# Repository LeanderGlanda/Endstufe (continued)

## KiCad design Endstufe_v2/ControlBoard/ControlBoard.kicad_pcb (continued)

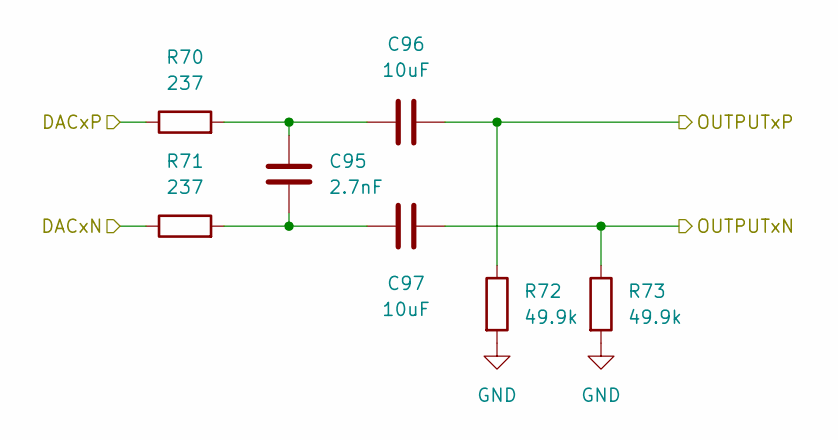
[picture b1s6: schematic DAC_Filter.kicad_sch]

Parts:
C95: 2.7nF; C_0402_1005Metric; LCSC C525230
C96, C97: 10uF; C_0805_2012Metric; LCSC Part # C440198
R70, R71: 237; R_0402_1005Metric; LCSC C2079916
R72, R73: 49.9k; R_0402_1005Metric; LCSC C854344

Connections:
/ADAU1962A/DAC1N: C97.1, R73.1; also elsewhere on the board
/ADAU1962A/DAC1P: C96.2, R72.1; also elsewhere on the board
/ADAU1962A/DAC_Filter11/DACxN: R71.1; also elsewhere on the board
/ADAU1962A/DAC_Filter11/DACxP: R70.1; also elsewhere on the board
GND: R72.2, R73.2; also elsewhere on the board
unnamed: C95.1, C97.2, R71.2
unnamed: C95.2, C96.1, R70.2

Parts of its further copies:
C62, C65, C68, C71, C74, C77, C80, C83, C86, C89, C92: 2.7nF; C_0402_1005Metric; LCSC C525230
C63, C64, C66, C67, C69, C70, C72, C73, C75, C76, C78, C79, C81, C82, C84, C85, C87, C88, C90, C91, C93, C94: 10uF; C_0805_2012Metric; LCSC Part # C440198
R26, R27, R30, R31, R34, R35, R38, R39, R42, R43, R46, R47, R50, R51, R54, R55, R58, R59, R62, R63, R66, R67: 237; R_0402_1005Metric; LCSC C2079916
R28, R29, R32, R33, R36, R37, R40, R41, R44, R45, R48, R49, R52, R53, R56, R57, R60, R61, R64, R65, R68, R69: 49.9k; R_0402_1005Metric; LCSC C854344

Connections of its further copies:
/ADAU1962A/DAC2N: C94.1, R69.1; also elsewhere on the board
/ADAU1962A/DAC2P: C93.2, R68.1; also elsewhere on the board
/ADAU1962A/DAC3N: C91.1, R65.1; also elsewhere on the board
/ADAU1962A/DAC3P: C90.2, R64.1; also elsewhere on the board
/ADAU1962A/DAC_Filter1/DACxN: R31.1; also elsewhere on the board
/ADAU1962A/DAC_Filter1/DACxP: R30.1; also elsewhere on the board
/ADAU1962A/DAC_Filter1/OUTPUTxN: C67.1, R33.1; also elsewhere on the board
/ADAU1962A/DAC_Filter1/OUTPUTxP: C66.2, R32.1; also elsewhere on the board
/ADAU1962A/DAC_Filter2/DACxN: R35.1; also elsewhere on the board
/ADAU1962A/DAC_Filter2/DACxP: R34.1; also elsewhere on the board
/ADAU1962A/DAC_Filter2/OUTPUTxN: C70.1, R37.1; also elsewhere on the board
/ADAU1962A/DAC_Filter2/OUTPUTxP: C69.2, R36.1; also elsewhere on the board
/ADAU1962A/DAC_Filter3/DACxN: R39.1; also elsewhere on the board
/ADAU1962A/DAC_Filter3/DACxP: R38.1; also elsewhere on the board
/ADAU1962A/DAC_Filter3/OUTPUTxN: C73.1, R41.1; also elsewhere on the board
/ADAU1962A/DAC_Filter3/OUTPUTxP: C72.2, R40.1; also elsewhere on the board
/ADAU1962A/DAC_Filter4/DACxN: R43.1; also elsewhere on the board
/ADAU1962A/DAC_Filter4/DACxP: R42.1; also elsewhere on the board
/ADAU1962A/DAC_Filter4/OUTPUTxN: C76.1, R45.1; also elsewhere on the board
/ADAU1962A/DAC_Filter4/OUTPUTxP: C75.2, R44.1; also elsewhere on the board
/ADAU1962A/DAC_Filter5/DACxN: R47.1; also elsewhere on the board
/ADAU1962A/DAC_Filter5/DACxP: R46.1; also elsewhere on the board
/ADAU1962A/DAC_Filter5/OUTPUTxN: C79.1, R49.1; also elsewhere on the board
/ADAU1962A/DAC_Filter5/OUTPUTxP: C78.2, R48.1; also elsewhere on the board
/ADAU1962A/DAC_Filter6/DACxN: R51.1; also elsewhere on the board
/ADAU1962A/DAC_Filter6/DACxP: R50.1; also elsewhere on the board
/ADAU1962A/DAC_Filter6/OUTPUTxN: C82.1, R53.1; also elsewhere on the board
/ADAU1962A/DAC_Filter6/OUTPUTxP: C81.2, R52.1; also elsewhere on the board
/ADAU1962A/DAC_Filter7/DACxN: R55.1; also elsewhere on the board
/ADAU1962A/DAC_Filter7/DACxP: R54.1; also elsewhere on the board
/ADAU1962A/DAC_Filter7/OUTPUTxN: C85.1, R57.1; also elsewhere on the board
/ADAU1962A/DAC_Filter7/OUTPUTxP: C84.2, R56.1; also elsewhere on the board
/ADAU1962A/DAC_Filter8/DACxN: R59.1; also elsewhere on the board
/ADAU1962A/DAC_Filter8/DACxP: R58.1; also elsewhere on the board
/ADAU1962A/DAC_Filter8/OUTPUTxN: C88.1, R61.1; also elsewhere on the board
/ADAU1962A/DAC_Filter8/OUTPUTxP: C87.2, R60.1; also elsewhere on the board
/ADAU1962A/DAC_Filter9/DACxN: R63.1; also elsewhere on the board
/ADAU1962A/DAC_Filter9/DACxP: R62.1; also elsewhere on the board
/ADAU1962A/DAC_Filter10/DACxN: R67.1; also elsewhere on the board
/ADAU1962A/DAC_Filter10/DACxP: R66.1; also elsewhere on the board
/ADAU1962A/DAC_Filter/DACxN: R27.1; also elsewhere on the board
/ADAU1962A/DAC_Filter/DACxP: R26.1; also elsewhere on the board
/ADAU1962A/DAC_Filter/OUTPUTxN: C64.1, R29.1; also elsewhere on the board
/ADAU1962A/DAC_Filter/OUTPUTxP: C63.2, R28.1; also elsewhere on the board
GND: R28.2, R29.2, R32.2, R33.2, R36.2, R37.2, R40.2, R41.2, R44.2, R45.2, R48.2, R49.2, R52.2, R53.2, R56.2, R57.2, R60.2, R61.2, R64.2, R65.2, R68.2, R69.2; also elsewhere on the board
unnamed: C62.1, C64.2, R27.2
unnamed: C62.2, C63.1, R26.2
unnamed: C65.1, C67.2, R31.2
unnamed: C65.2, C66.1, R30.2
unnamed: C68.1, C70.2, R35.2
unnamed: C68.2, C69.1, R34.2
unnamed: C71.1, C73.2, R39.2
unnamed: C71.2, C72.1, R38.2
unnamed: C74.1, C76.2, R43.2
unnamed: C74.2, C75.1, R42.2
unnamed: C77.1, C79.2, R47.2
unnamed: C77.2, C78.1, R46.2
unnamed: C80.1, C82.2, R51.2
unnamed: C80.2, C81.1, R50.2
unnamed: C83.1, C85.2, R55.2
unnamed: C83.2, C84.1, R54.2
unnamed: C86.1, C88.2, R59.2
unnamed: C86.2, C87.1, R58.2
unnamed: C89.1, C91.2, R63.2
unnamed: C89.2, C90.1, R62.2
unnamed: C92.1, C94.2, R67.2
unnamed: C92.2, C93.1, R66.2

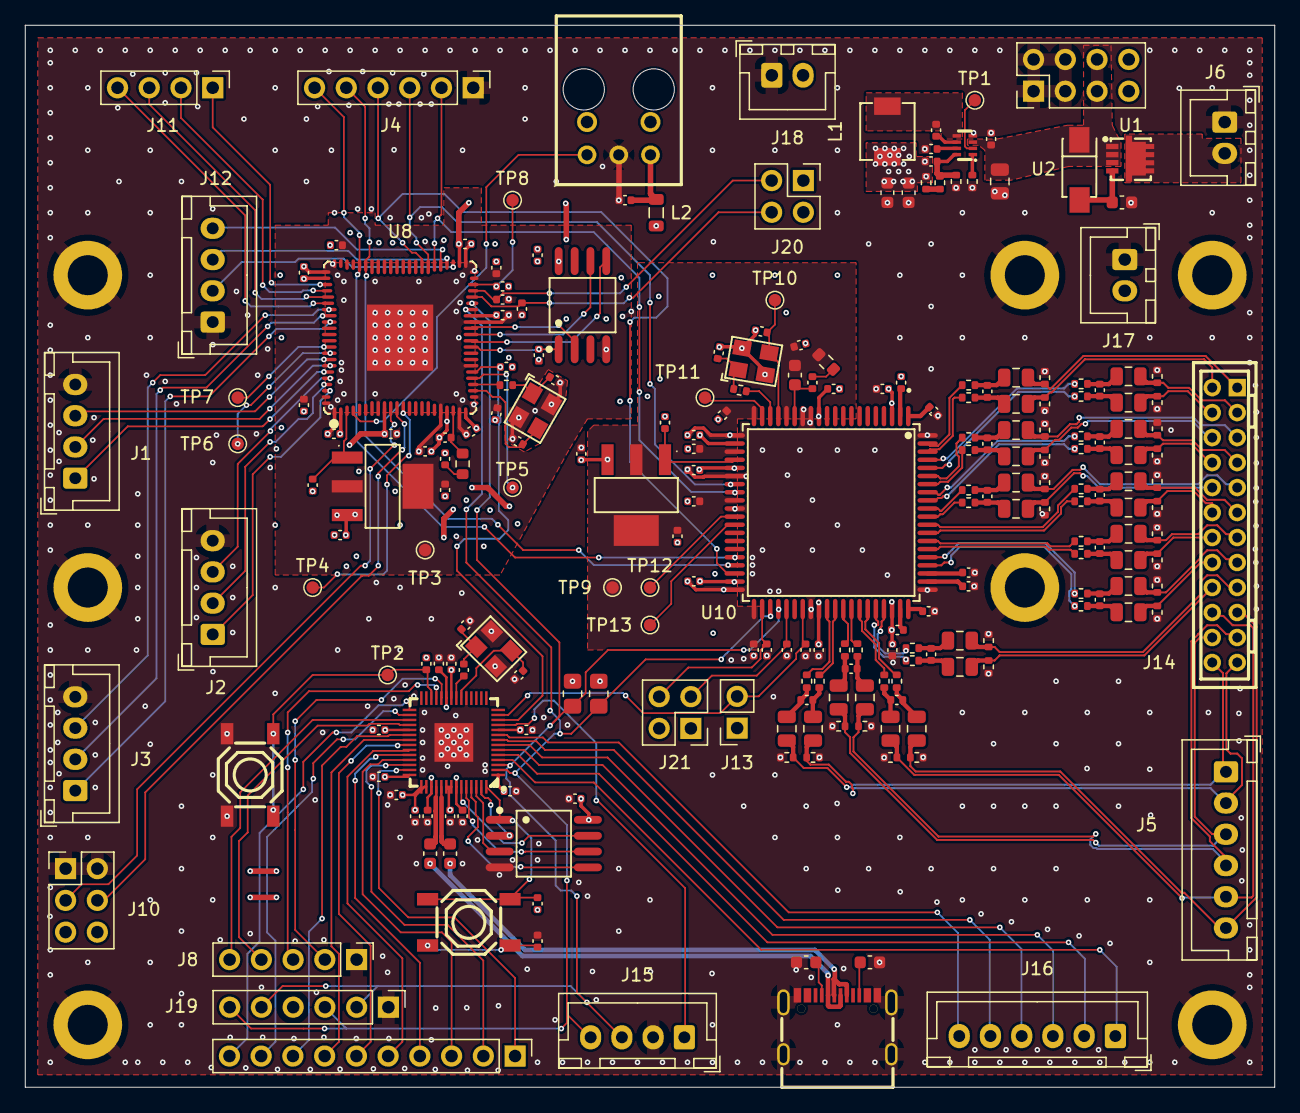
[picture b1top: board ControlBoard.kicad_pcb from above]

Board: 4 copper layers, 100.0 x 85.0 mm, 237 parts (0 on the bottom side), 188 nets.

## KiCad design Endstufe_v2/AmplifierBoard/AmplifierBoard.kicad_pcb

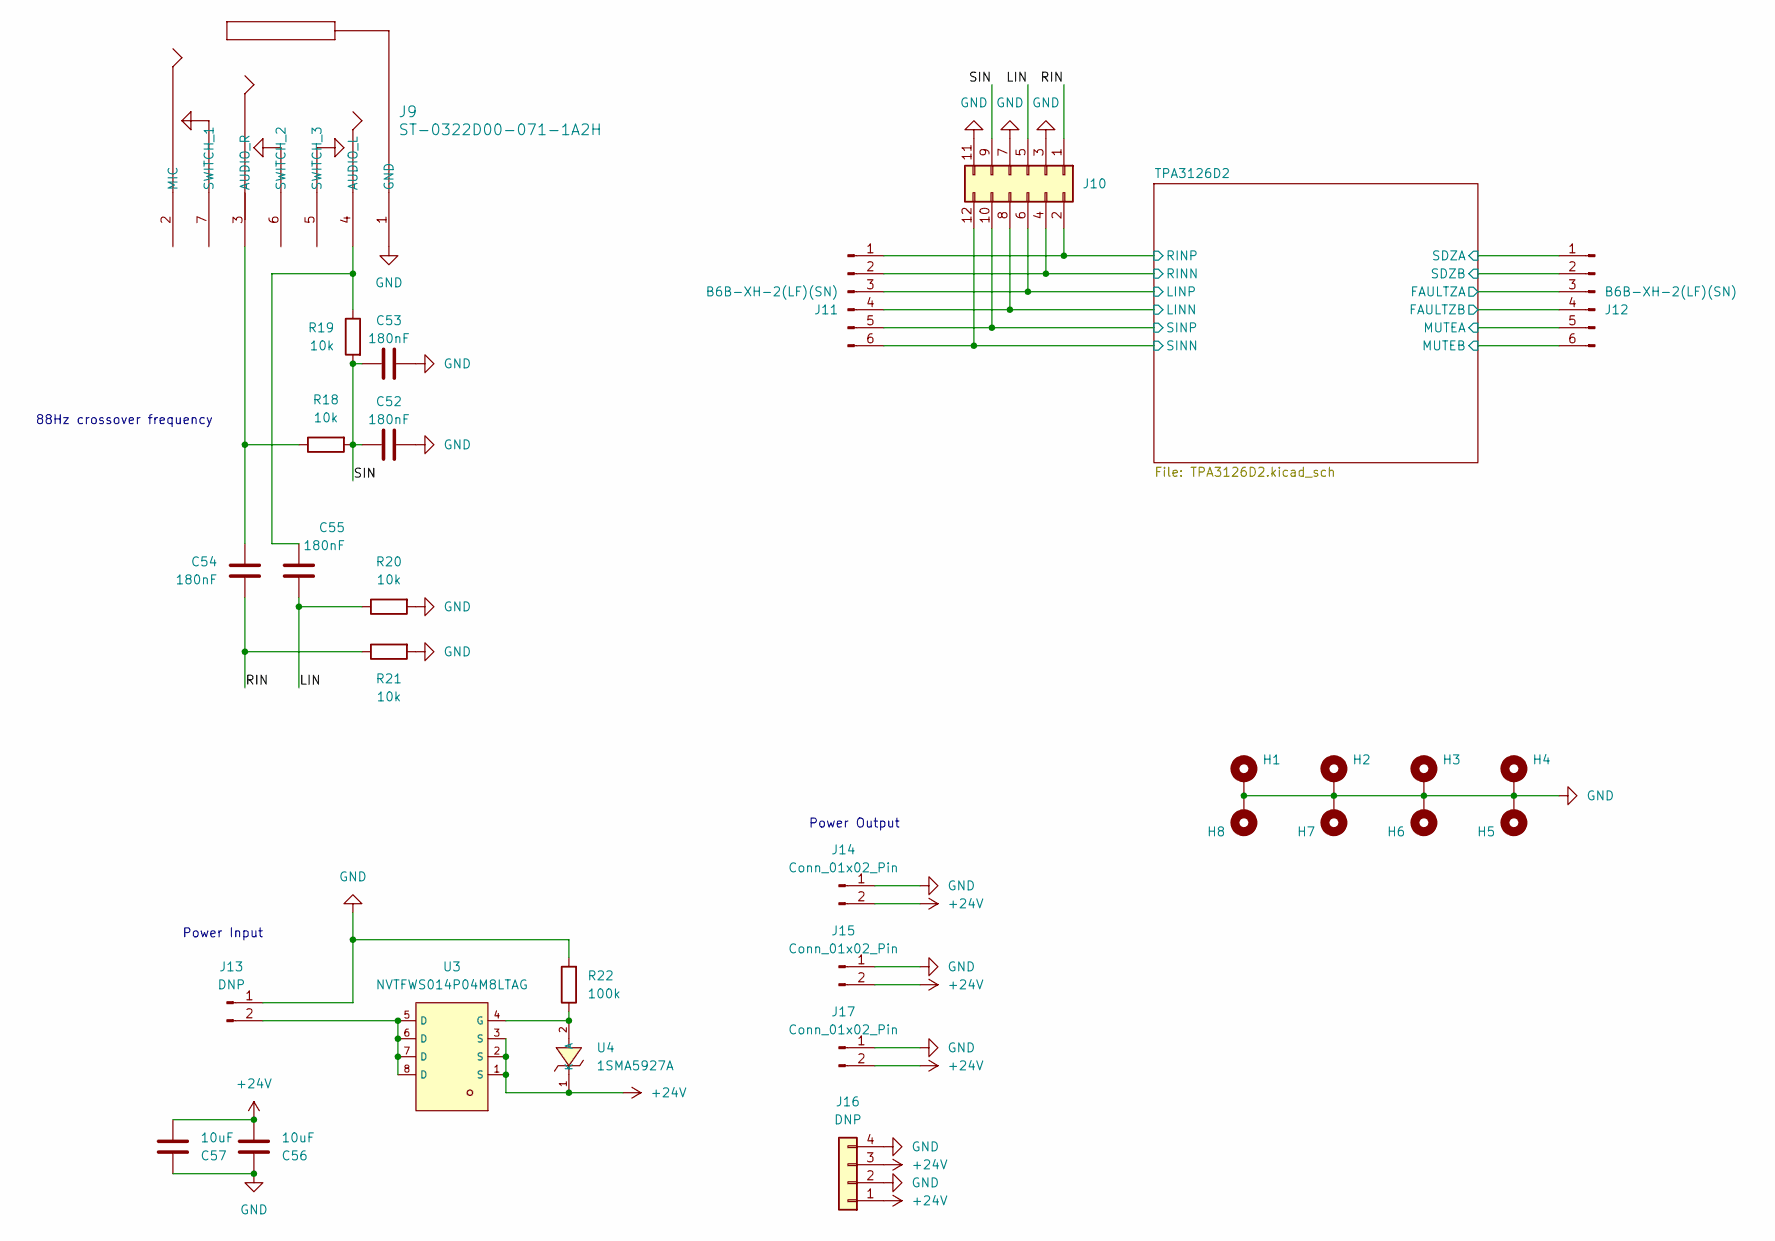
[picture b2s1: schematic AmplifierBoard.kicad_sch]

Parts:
C52, C53, C54, C55: 180nF; C_0603_1608Metric; LCSC C2760543
C56, C57: 10uF; C_1206_3216Metric; LCSC Part # C89632
H1, H2, H3, H4: MountingHole_Pad; MountingHole_2.2mm_M2_ISO7380_Pad
H5, H6, H7, H8: MountingHole_Pad; MountingHole_3.2mm_M3_ISO14580_Pad
J9: ST-0322D00-071-1A2H; AUDIO-TH_ST-0322D00-071-1A2H; LCSC Part # C2829970
J10: DNP; PinHeader_2x06_P2.54mm_Vertical
J11, J12: B6B-XH-2(LF)(SN); JST_XH_B6B-XH-A_1x06_P2.50mm_Vertical; LCSC C157986
J13: DNP; Molex_Sabre_43160-1102_1x02_P7.49mm_Horizontal
J14, J15, J17: Conn_01x02_Pin; JST_XH_B2B-XH-A_1x02_P2.50mm_Vertical; LCSC Part # C158012
J16: DNP; PinHeader_1x04_P2.54mm_Vertical
R18, R19, R20, R21: 10k; C_0402_1005Metric; LCSC Part # C25744
R22: 100k; C_0603_1608Metric; LCSC C25803
U3: NVTFWS014P04M8LTAG; POWERPAK-1212-8_L3.1-W3.1-P0.65-LS3.3-BL-SIS402DN-T1-GE3; LCSC C900554
U4: 1SMA5927A; SMA_L4.3-W2.6-LS5.0-RD; LCSC C19077489

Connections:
+24V: C56.2, C57.2, J14.2, J15.2, J16.1, J16.3, J17.2, U3.1 (S), U3.2 (S), U3.3 (S), U4.1 (K); also elsewhere on the board
/LIN: C55.1, J10.5, R20.1
/RIN: C54.2, J10.1, R21.1
/SIN: C52.2, C53.2, J10.9, R18.2, R19.2
/TPA3126D2/FAULTZA: J12.3; also elsewhere on the board
/TPA3126D2/FAULTZB: J12.4; also elsewhere on the board
/TPA3126D2/LINN: J10.8, J11.4; also elsewhere on the board
/TPA3126D2/LINP: J10.6, J11.3; also elsewhere on the board
/TPA3126D2/MUTEA: J12.5; also elsewhere on the board
/TPA3126D2/MUTEB: J12.6; also elsewhere on the board
/TPA3126D2/RINN: J10.4, J11.2; also elsewhere on the board
/TPA3126D2/RINP: J10.2, J11.1; also elsewhere on the board
/TPA3126D2/SDZA: J12.1; also elsewhere on the board
/TPA3126D2/SDZB: J12.2; also elsewhere on the board
/TPA3126D2/SINN: J10.12, J11.6; also elsewhere on the board
/TPA3126D2/SINP: J10.10, J11.5; also elsewhere on the board
GND: C52.1, C53.1, C56.1, C57.1, H1.1, H2.1, H3.1, H4.1, H5.1, H6.1, H7.1, H8.1, J9.1 (GND), J10.3, J10.7, J10.11, J13.1, J14.1, J15.1, J16.2, J16.4, J17.1, R20.2, R21.2, R22.2; also elsewhere on the board
unnamed: C55.2, J9.4 (AUDIO_L), R19.1
unnamed: C54.1, J9.3 (AUDIO_R), R18.1
unnamed: J13.2, U3.5 (D), U3.6 (D), U3.7 (D), U3.8 (D)
unnamed: R22.1, U3.4 (G), U4.2 (A)

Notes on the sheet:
Power Input
88Hz crossover frequency
Power Output

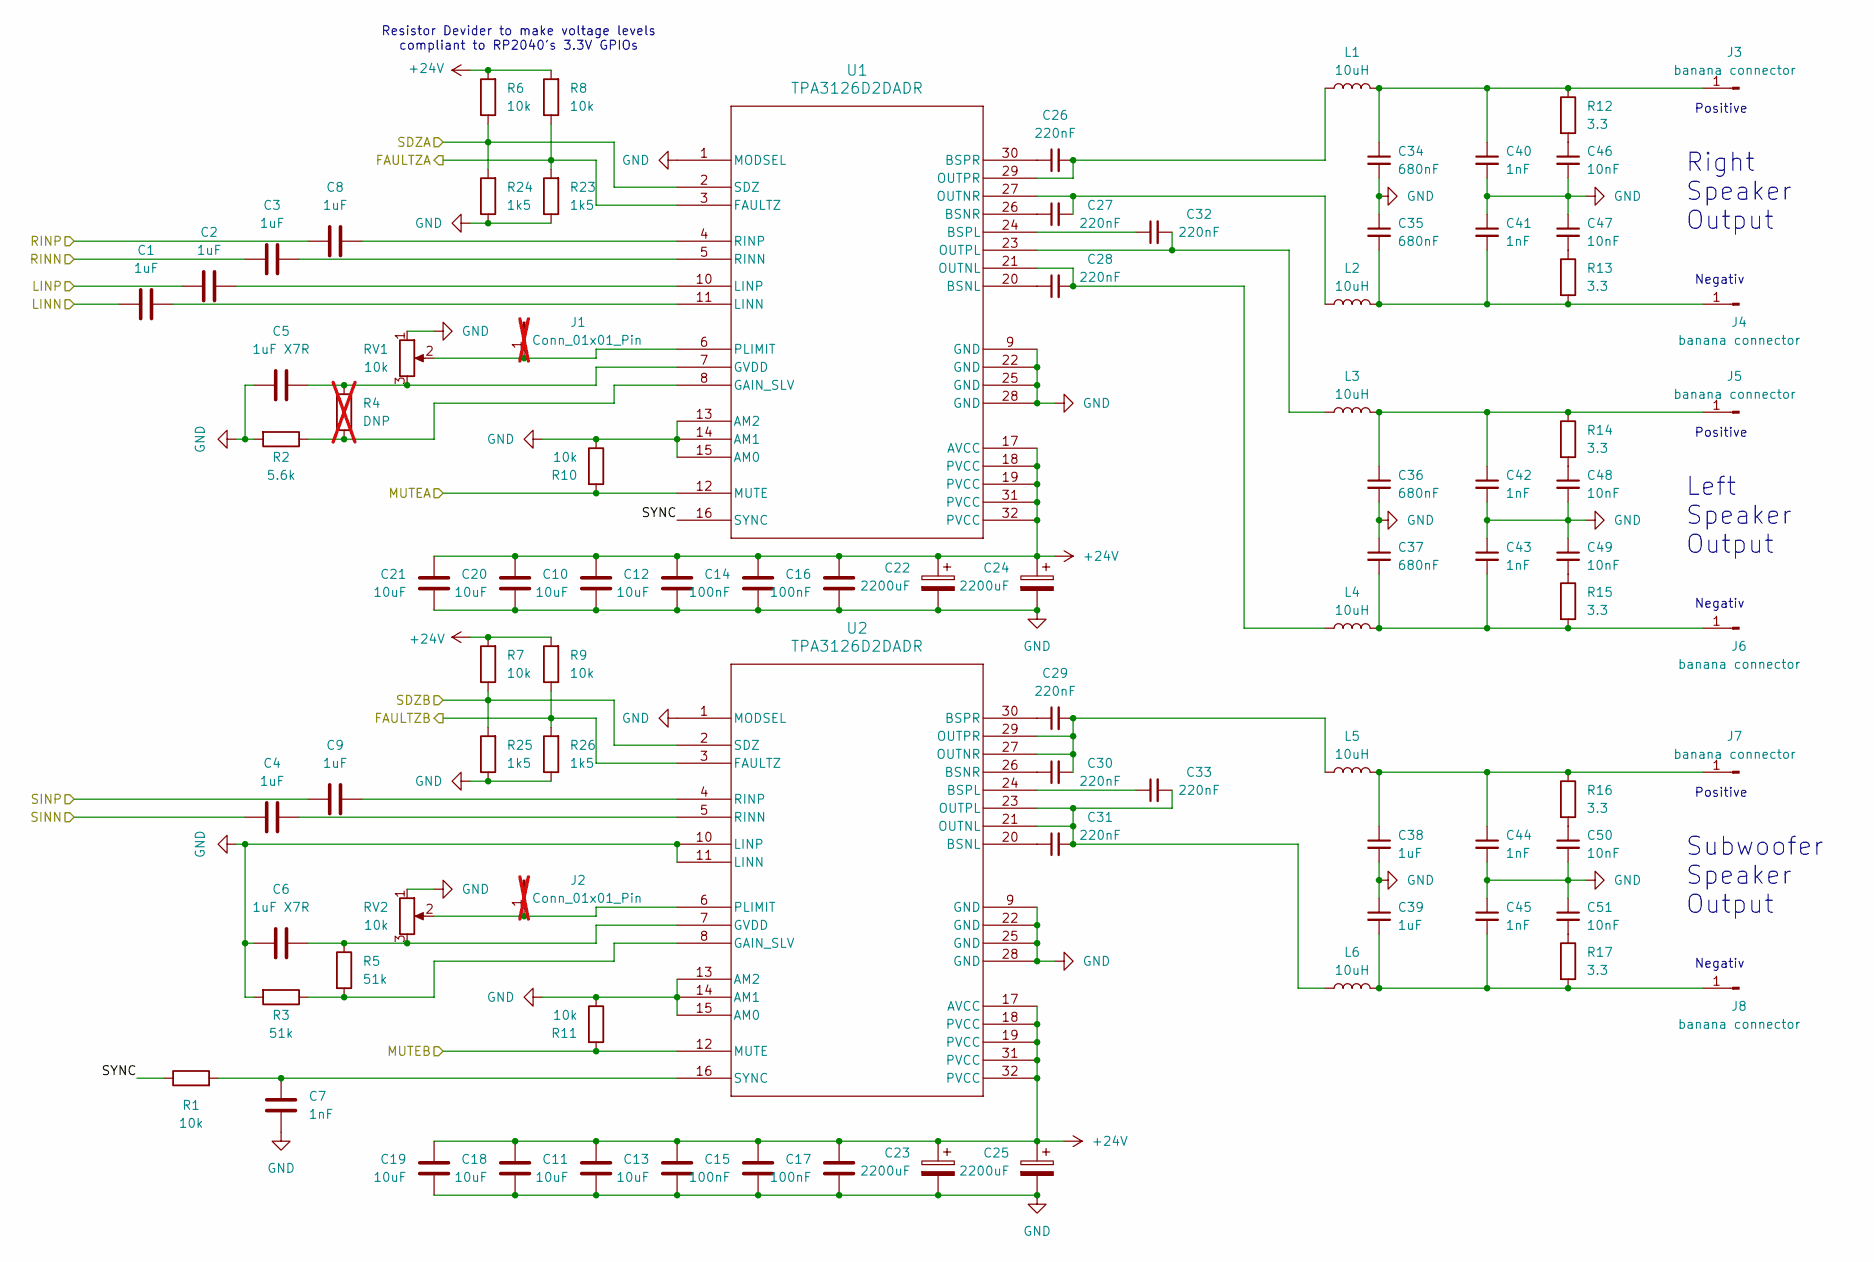
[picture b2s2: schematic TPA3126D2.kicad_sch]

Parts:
C1, C2, C3, C4, C8, C9, C38, C39: 1uF; C_0805_2012Metric; LCSC Part # C28323
C5, C6: 1uF X7R; C_0805_2012Metric; LCSC Part # C28323
C7, C40, C41, C42, C43, C44, C45: 1nF; C_1206_3216Metric; LCSC Part # C5137603
C10, C11, C12, C13, C18, C19, C20, C21: 10uF; C_1206_3216Metric; LCSC Part # C89632
C14, C15, C16, C17: 100nF; C_0402_1005Metric; LCSC Part # C307331
C22, C23, C24, C25: 2200uF; CP_Radial_D18.0mm_P7.50mm; LCSC Part # C443034
C26, C27, C28, C29, C30, C31, C32, C33: 220nF; C_0805_2012Metric; LCSC Part # C5378
C34, C35, C36, C37: 680nF; C_1206_3216Metric; LCSC Part # C2835168
C46, C47, C48, C49, C50, C51: 10nF; C_1206_3216Metric; LCSC Part # C9194
J1, J2: Conn_01x01_Pin; PinHeader_1x01_P2.54mm_Vertical; not fitted
J3, J4, J5, J6, J7, J8: banana connector; CONN_973582100_HRS
L1, L2, L3, L4, L5, L6: 10uH; IND-SMD_L8.5-W8.0_PCC-M0854M; LCSC Part # C2962885
R1, R6, R7, R8, R9, R10, R11: 10k; C_0402_1005Metric; LCSC Part # C25744
R2: 5.6k; R_0603_1608Metric; LCSC Part # C23189
R3, R5: 51k; R_0402_1005Metric; LCSC Part # C25794
R4: DNP; R_0805_2012Metric; not fitted
R12, R13, R14, R15, R16, R17: 3.3; R_1206_3216Metric; LCSC Part # C2930397
R23, R24, R25, R26: 1k5; C_0402_1005Metric; LCSC Part # C431791
RV1, RV2: 10k; Potentiometer_Bourns_3314G_Vertical; LCSC Part # C780220
U1, U2: TPA3126D2DADR; HTSSOP-32_L11.0-W6.1-P0.65-LS8.1-BL; LCSC Part # C544472

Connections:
+24V: C10.1, C11.1, C12.1, C13.1, C14.1, C15.1, C16.1, C17.1, C18.1, C19.1, C20.1, C21.1, C22.1, C23.1, C24.1, C25.1, R6.2, R7.2, R8.2, R9.2, U1.17 (AVCC), U1.18 (PVCC), U1.19 (PVCC), U1.31 (PVCC), U1.32 (PVCC), U2.17 (AVCC), U2.18 (PVCC), U2.19 (PVCC), U2.31 (PVCC), U2.32 (PVCC); also elsewhere on the board
/TPA3126D2/FAULTZA: R8.1, R23.2, U1.3 (FAULTZ); also elsewhere on the board
/TPA3126D2/FAULTZB: R9.1, R26.2, U2.3 (FAULTZ); also elsewhere on the board
/TPA3126D2/LINN: C1.1; also elsewhere on the board
/TPA3126D2/LINP: C2.1; also elsewhere on the board
/TPA3126D2/MUTEA: R10.2, U1.12 (MUTE); also elsewhere on the board
/TPA3126D2/MUTEB: R11.2, U2.12 (MUTE); also elsewhere on the board
/TPA3126D2/RINN: C3.1; also elsewhere on the board
/TPA3126D2/RINP: C8.1; also elsewhere on the board
/TPA3126D2/SDZA: R6.1, R24.2, U1.2 (SDZ); also elsewhere on the board
/TPA3126D2/SDZB: R7.1, R25.2, U2.2 (SDZ); also elsewhere on the board
/TPA3126D2/SINN: C4.1; also elsewhere on the board
/TPA3126D2/SINP: C9.1; also elsewhere on the board
/TPA3126D2/SYNC: R1.1, U1.16 (SYNC)
GND: C5.1, C6.1, C7.2, C10.2, C11.2, C12.2, C13.2, C14.2, C15.2, C16.2, C17.2, C18.2, C19.2, C20.2, C21.2, C22.2, C23.2, C24.2, C25.2, C34.2, C35.1, C36.2, C37.1, C38.2, C39.1, C40.2, C41.1, C42.2, C43.1, C44.2, C45.1, C46.2, C47.1, C48.2, C49.1, C50.2, C51.1, R2.2, R3.2, R10.1, R11.1, R23.1, R24.1, R25.1, R26.1, RV1.1, RV2.1, U1.1 (MODSEL), U1.9 (GND), U1.13 (AM2), U1.14 (AM1), U1.15 (AM0), U1.22 (GND), U1.25 (GND), U1.28 (GND), U2.1 (MODSEL), U2.9 (GND), U2.10 (LINP), U2.11 (LINN), U2.13 (AM2), U2.14 (AM1), U2.15 (AM0), U2.22 (GND), U2.25 (GND), U2.28 (GND); also elsewhere on the board
unnamed: C46.1, R12.2
unnamed: C47.2, R13.1
unnamed: C48.1, R14.2
unnamed: C49.2, R15.1
unnamed: C50.1, R16.2
unnamed: C51.2, R17.1
unnamed: J1.1, RV1.2, U1.6 (PLIMIT)
unnamed: J2.1, RV2.2, U2.6 (PLIMIT)
unnamed: C34.1, C40.1, J3.1, L1.2, R12.1
unnamed: C35.2, C41.2, J4.1, L2.2, R13.2
unnamed: C36.1, C42.1, J5.1, L3.2, R14.1
unnamed: C37.2, C43.2, J6.1, L4.2, R15.2
unnamed: C38.1, C44.1, J7.1, L5.2, R16.1
unnamed: C39.2, C45.2, J8.1, L6.2, R17.2
unnamed: C28.1, U1.20 (BSNL)
unnamed: C27.1, U1.26 (BSNR)
unnamed: C32.1, U1.24 (BSPL)
unnamed: C26.1, U1.30 (BSPR)
unnamed: R2.1, R4.2, U1.8 (GAIN_SLV)
unnamed: C5.2, R4.1, RV1.3, U1.7 (GVDD)
unnamed: C1.2, U1.11 (LINN)
unnamed: C2.2, U1.10 (LINP)
unnamed: C28.2, L4.1, U1.21 (OUTNL)
unnamed: C27.2, L2.1, U1.27 (OUTNR)
unnamed: C32.2, L3.1, U1.23 (OUTPL)
unnamed: C26.2, L1.1, U1.29 (OUTPR)
unnamed: C3.2, U1.5 (RINN)
unnamed: C8.2, U1.4 (RINP)
unnamed: C31.1, U2.20 (BSNL)
unnamed: C30.1, U2.26 (BSNR)
unnamed: C33.1, U2.24 (BSPL)
unnamed: C29.1, U2.30 (BSPR)
unnamed: R3.1, R5.2, U2.8 (GAIN_SLV)
unnamed: C6.2, R5.1, RV2.3, U2.7 (GVDD)
unnamed: C31.2, C33.2, L6.1, U2.21 (OUTNL), U2.23 (OUTPL)
unnamed: C29.2, C30.2, L5.1, U2.27 (OUTNR), U2.29 (OUTPR)
unnamed: C4.2, U2.5 (RINN)
unnamed: C9.2, U2.4 (RINP)
unnamed: C7.1, R1.2, U2.16 (SYNC)

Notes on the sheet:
Positive
Negativ
Resistor Devider to make voltage levels compliant to RP2040's 3.3V GPIOs
Subwoofer Speaker Output
Right Speaker Output
Left Speaker Output

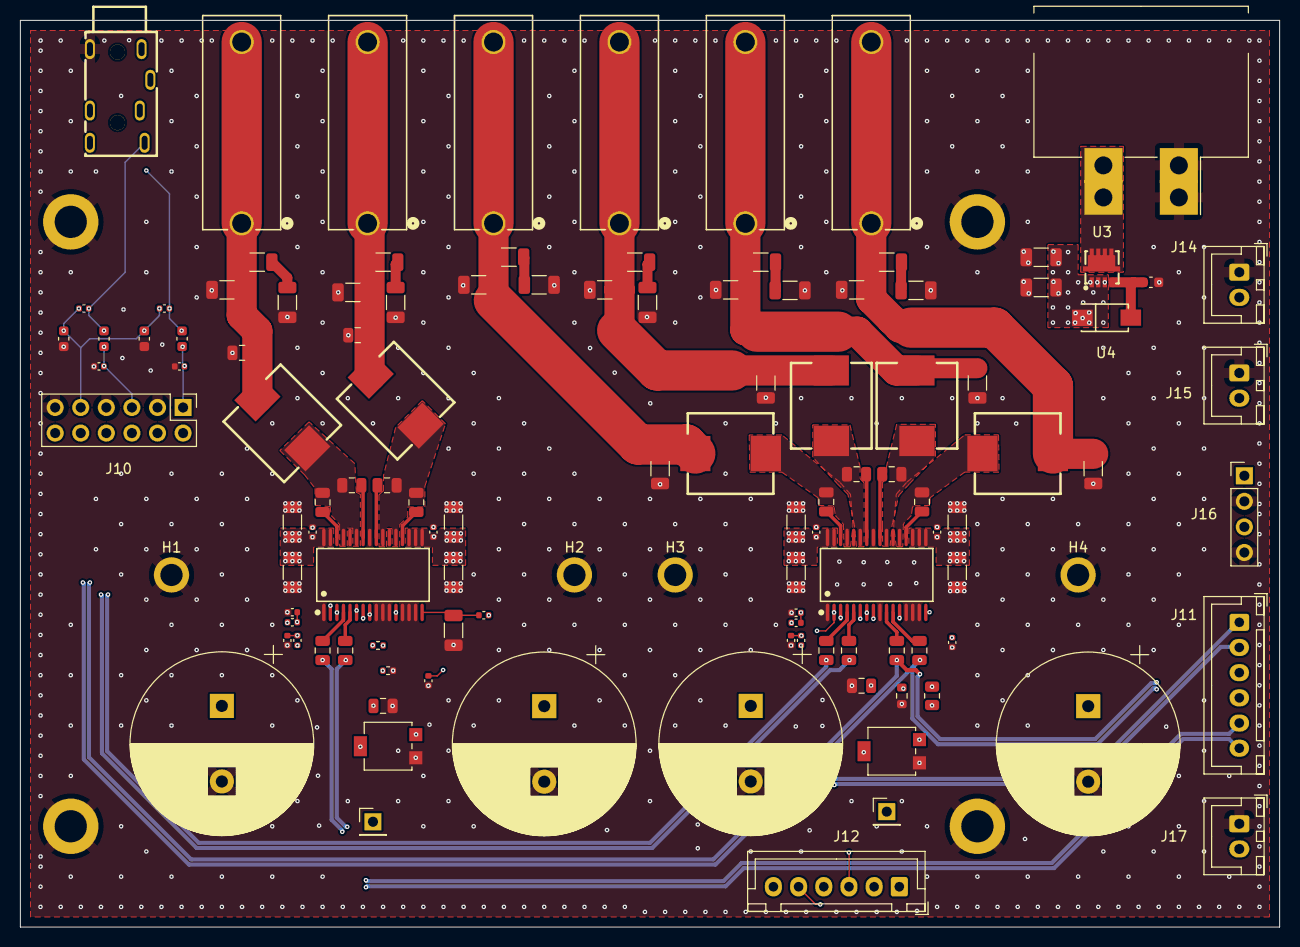
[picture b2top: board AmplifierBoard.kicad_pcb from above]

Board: 4 copper layers, 125.0 x 90.0 mm, 120 parts (0 on the bottom side), 61 nets.

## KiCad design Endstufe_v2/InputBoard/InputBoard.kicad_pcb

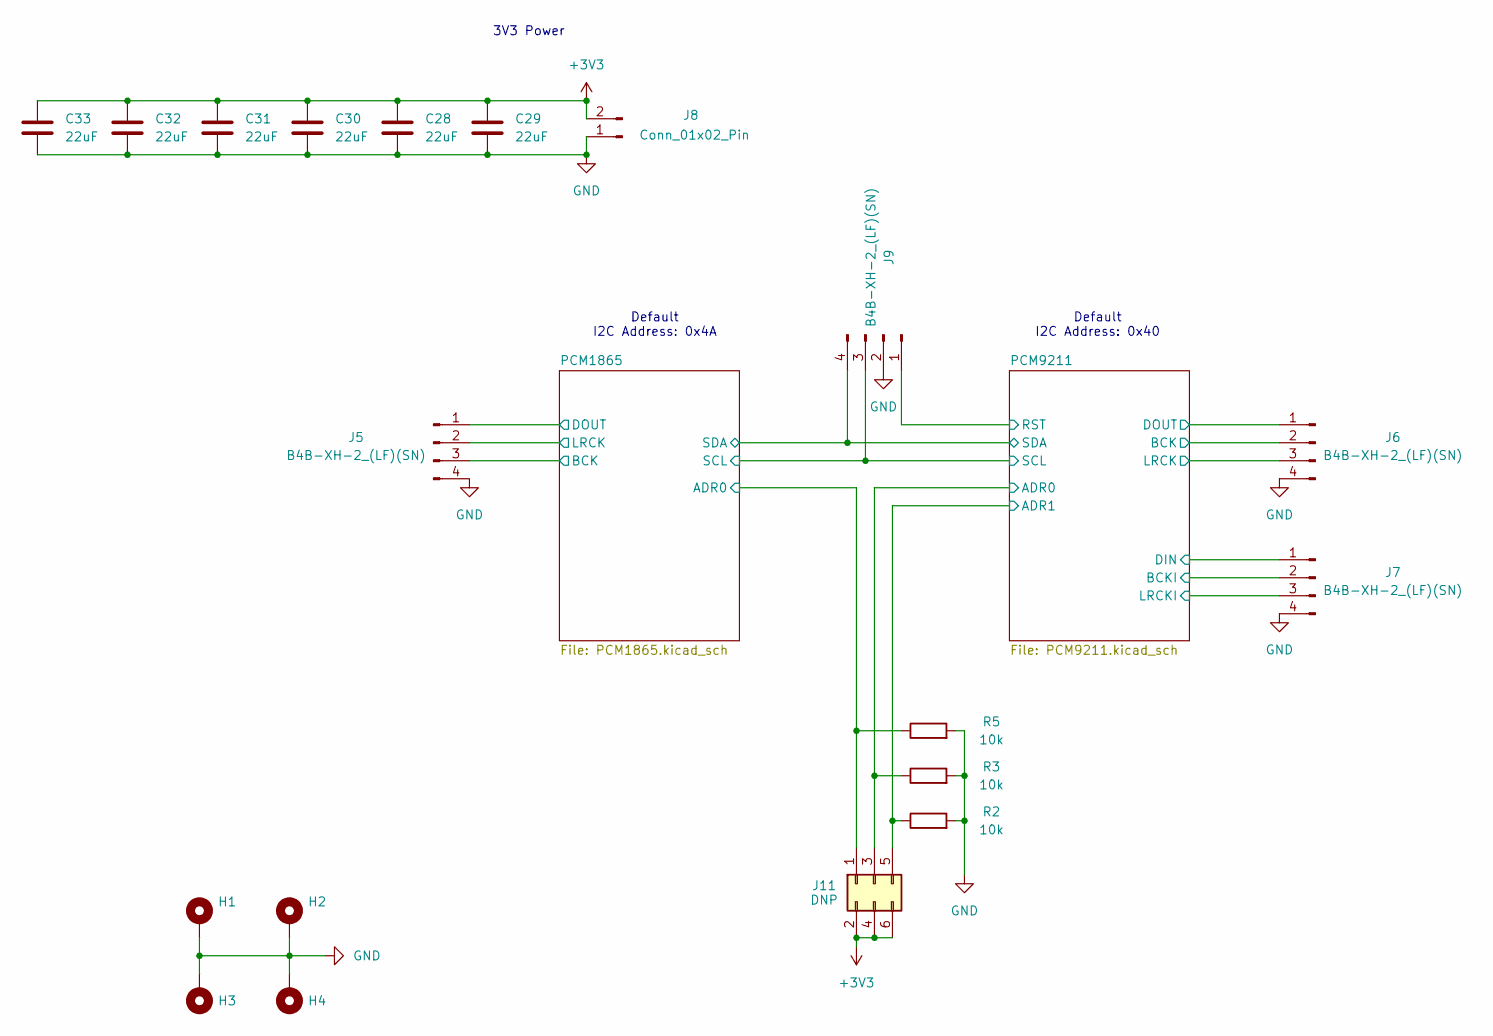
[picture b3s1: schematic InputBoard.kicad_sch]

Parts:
C28, C29, C30, C31, C32, C33: 22uF; C_0603_1608Metric; LCSC Part # C59461
H1, H2, H3, H4: MountingHole_Pad; MountingHole_3.2mm_M3_ISO14580_Pad
J5, J6, J7, J9: B4B-XH-2_(LF)(SN); JST_XH_B4B-XH-A_1x04_P2.50mm_Vertical; LCSC C157999
J8: Conn_01x02_Pin; JST_XH_B2B-XH-A_1x02_P2.50mm_Vertical; LCSC Part # C158012
J11: DNP; PinHeader_2x03_P2.54mm_Vertical
R2, R3, R5: 10k; C_0402_1005Metric; LCSC Part # C25744

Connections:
+3V3: C28.1, C29.1, C30.1, C31.1, C32.1, C33.1, J8.2, J11.2, J11.4, J11.6; also elsewhere on the board
/PCM1865/ADR0: J11.1, R5.1; also elsewhere on the board
/PCM1865/BCK: J5.3; also elsewhere on the board
/PCM1865/DOUT: J5.1; also elsewhere on the board
/PCM1865/LRCK: J5.2; also elsewhere on the board
/PCM1865/SCL: J9.3; also elsewhere on the board
/PCM1865/SDA: J9.4; also elsewhere on the board
/PCM9211/ADR0: J11.3, R3.1; also elsewhere on the board
/PCM9211/ADR1: J11.5, R2.1; also elsewhere on the board
/PCM9211/BCK: J6.2; also elsewhere on the board
/PCM9211/BCKI: J7.2; also elsewhere on the board
/PCM9211/DIN: J7.1; also elsewhere on the board
/PCM9211/DOUT: J6.1; also elsewhere on the board
/PCM9211/LRCK: J6.3; also elsewhere on the board
/PCM9211/LRCKI: J7.3; also elsewhere on the board
/PCM9211/RST: J9.1; also elsewhere on the board
GND: C28.2, C29.2, C30.2, C31.2, C32.2, C33.2, H1.1, H2.1, H3.1, H4.1, J5.4, J6.4, J7.4, J8.1, J9.2, R2.2, R3.2, R5.2; also elsewhere on the board

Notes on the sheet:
Default I2C Address: 0x40
3V3 Power
Default I2C Address: 0x4A

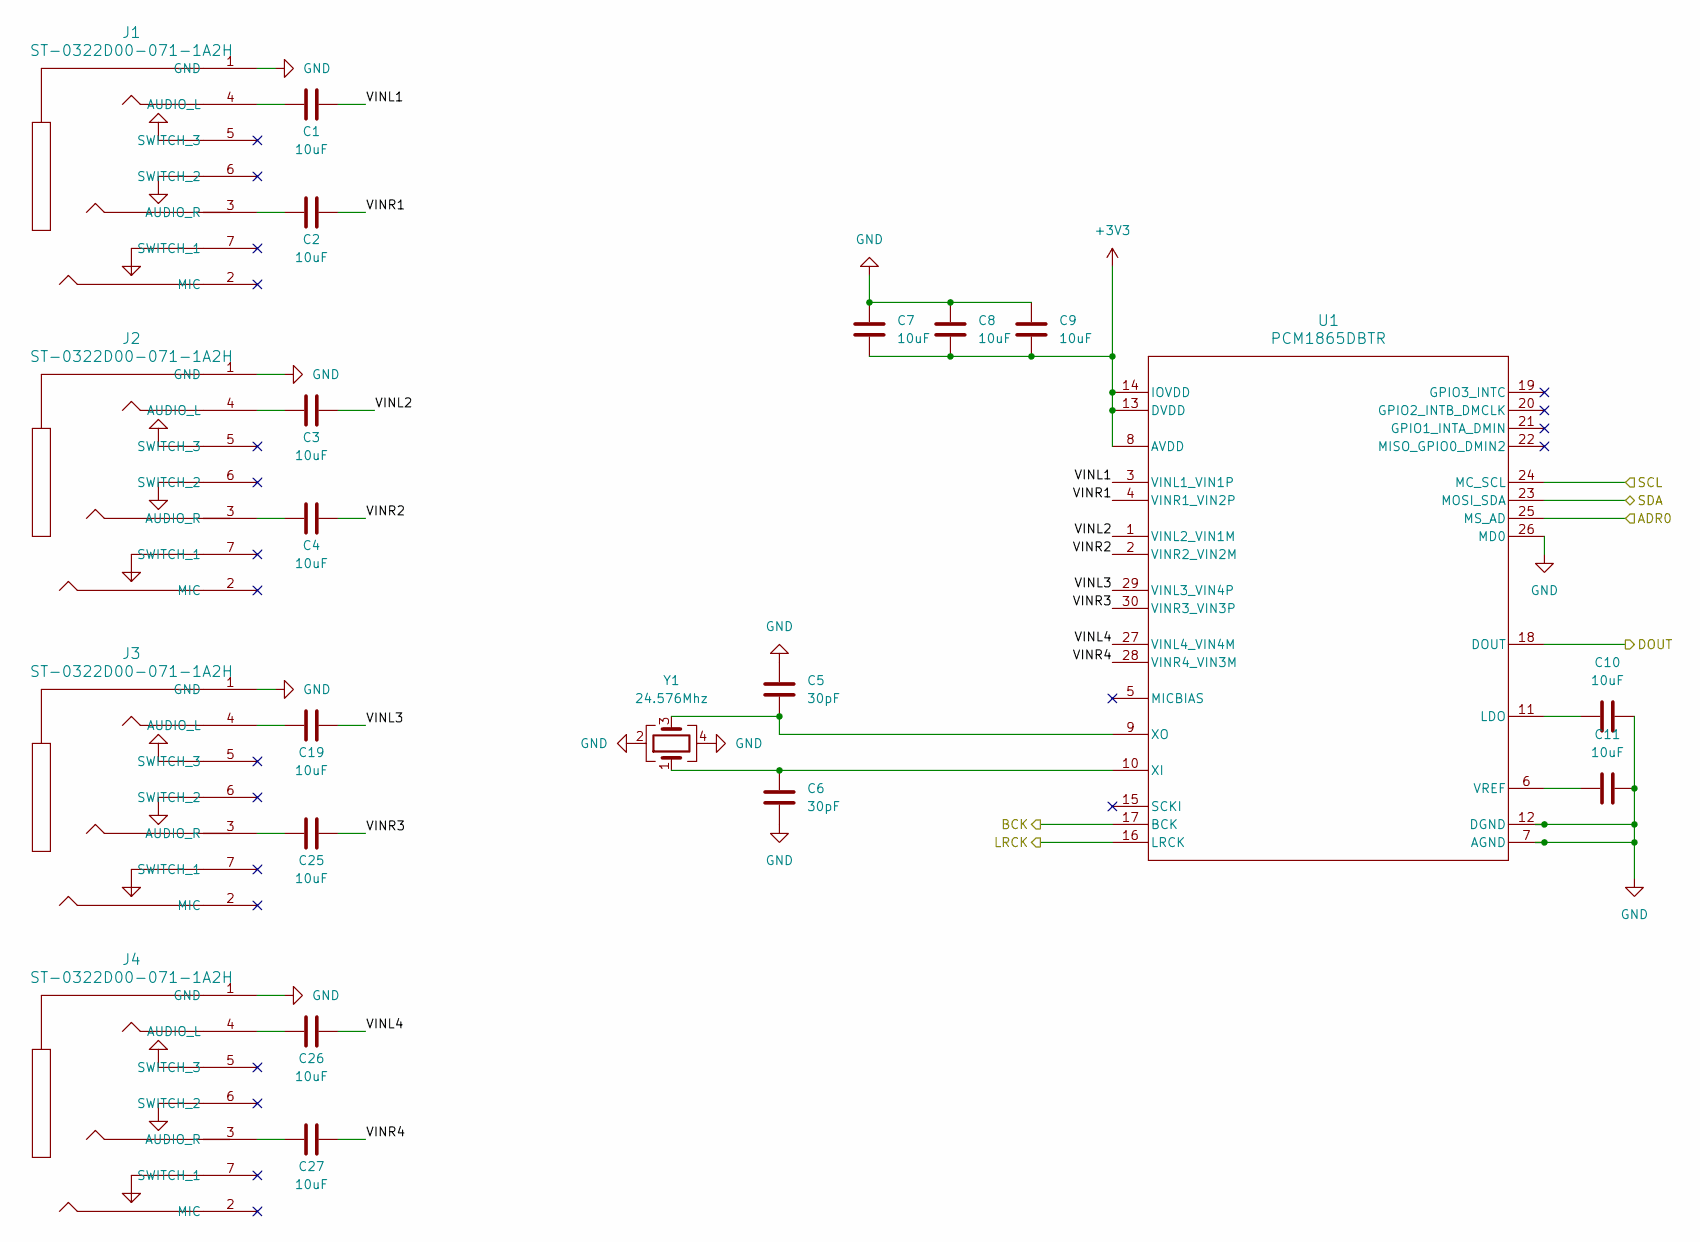
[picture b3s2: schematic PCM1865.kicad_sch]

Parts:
C1, C2, C3, C4, C19, C25, C26, C27: 10uF; C_0805_2012Metric; LCSC Part # C15850
C5, C6: 30pF; C_0402_1005Metric; LCSC Part # C526980
C7, C8, C9, C10, C11: 10uF; C_0402_1005Metric; LCSC Part # C15525
J1, J2, J3, J4: ST-0322D00-071-1A2H; AUDIO-TH_ST-0322D00-071-1A2H; LCSC Part # C2829970
U1: PCM1865DBTR; TSSOP-30_L7.8-W4.4-P0.50-LS6.4-BL; LCSC Part # C181312
Y1: 24.576Mhz; OSC-SMD_4P-L3.2-W2.5-BL; LCSC Part # C2901683

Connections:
+3V3: C7.2, C8.2, C9.2, U1.8 (AVDD), U1.13 (DVDD), U1.14 (IOVDD); also elsewhere on the board
/PCM1865/ADR0: U1.25 (MS_AD); also elsewhere on the board
/PCM1865/BCK: U1.17 (BCK); also elsewhere on the board
/PCM1865/DOUT: U1.18 (DOUT); also elsewhere on the board
/PCM1865/LRCK: U1.16 (LRCK); also elsewhere on the board
/PCM1865/SCL: U1.24 (MC_SCL); also elsewhere on the board
/PCM1865/SDA: U1.23 (MOSI_SDA); also elsewhere on the board
/PCM1865/VINL1: C1.2, U1.3 (VINL1_VIN1P)
/PCM1865/VINL2: C3.2, U1.1 (VINL2_VIN1M)
/PCM1865/VINL3: C19.2, U1.29 (VINL3_VIN4P)
/PCM1865/VINL4: C26.2, U1.27 (VINL4_VIN4M)
/PCM1865/VINR1: C2.2, U1.4 (VINR1_VIN2P)
/PCM1865/VINR2: C4.2, U1.2 (VINR2_VIN2M)
/PCM1865/VINR3: C25.2, U1.30 (VINR3_VIN3P)
/PCM1865/VINR4: C27.2, U1.28 (VINR4_VIN3M)
GND: C5.1, C6.2, C7.1, C8.1, C9.1, C10.2, C11.2, J1.1 (GND), J2.1 (GND), J3.1 (GND), J4.1 (GND), U1.7 (AGND), U1.12 (DGND), U1.26 (MD0), Y1.2, Y1.4; also elsewhere on the board
unnamed: C1.1, J1.4 (AUDIO_L)
unnamed: C2.1, J1.3 (AUDIO_R)
unnamed: C3.1, J2.4 (AUDIO_L)
unnamed: C4.1, J2.3 (AUDIO_R)
unnamed: C19.1, J3.4 (AUDIO_L)
unnamed: C25.1, J3.3 (AUDIO_R)
unnamed: C26.1, J4.4 (AUDIO_L)
unnamed: C27.1, J4.3 (AUDIO_R)
unnamed: C10.1, U1.11 (LDO)
unnamed: C11.1, U1.6 (VREF)
unnamed: C6.1, U1.10 (XI), Y1.1
unnamed: C5.2, U1.9 (XO), Y1.3
